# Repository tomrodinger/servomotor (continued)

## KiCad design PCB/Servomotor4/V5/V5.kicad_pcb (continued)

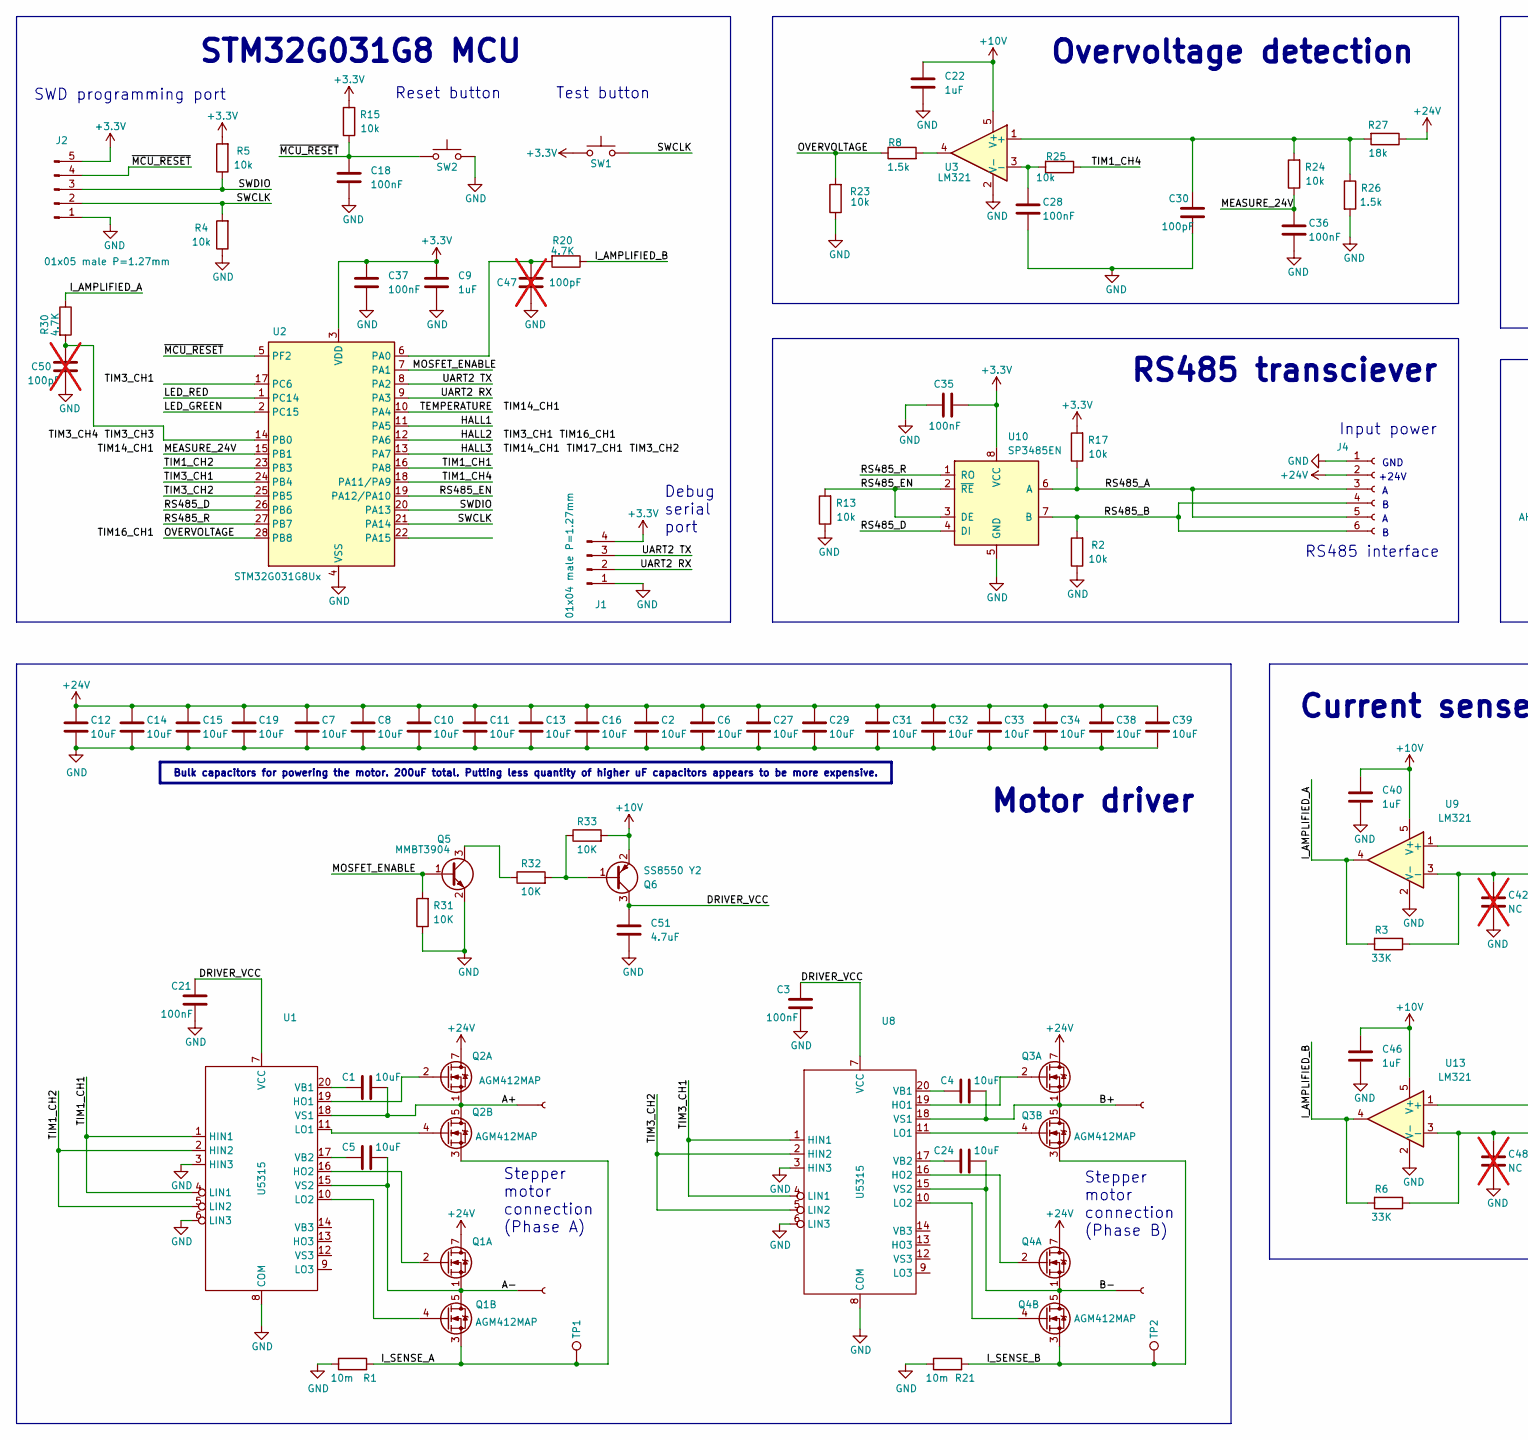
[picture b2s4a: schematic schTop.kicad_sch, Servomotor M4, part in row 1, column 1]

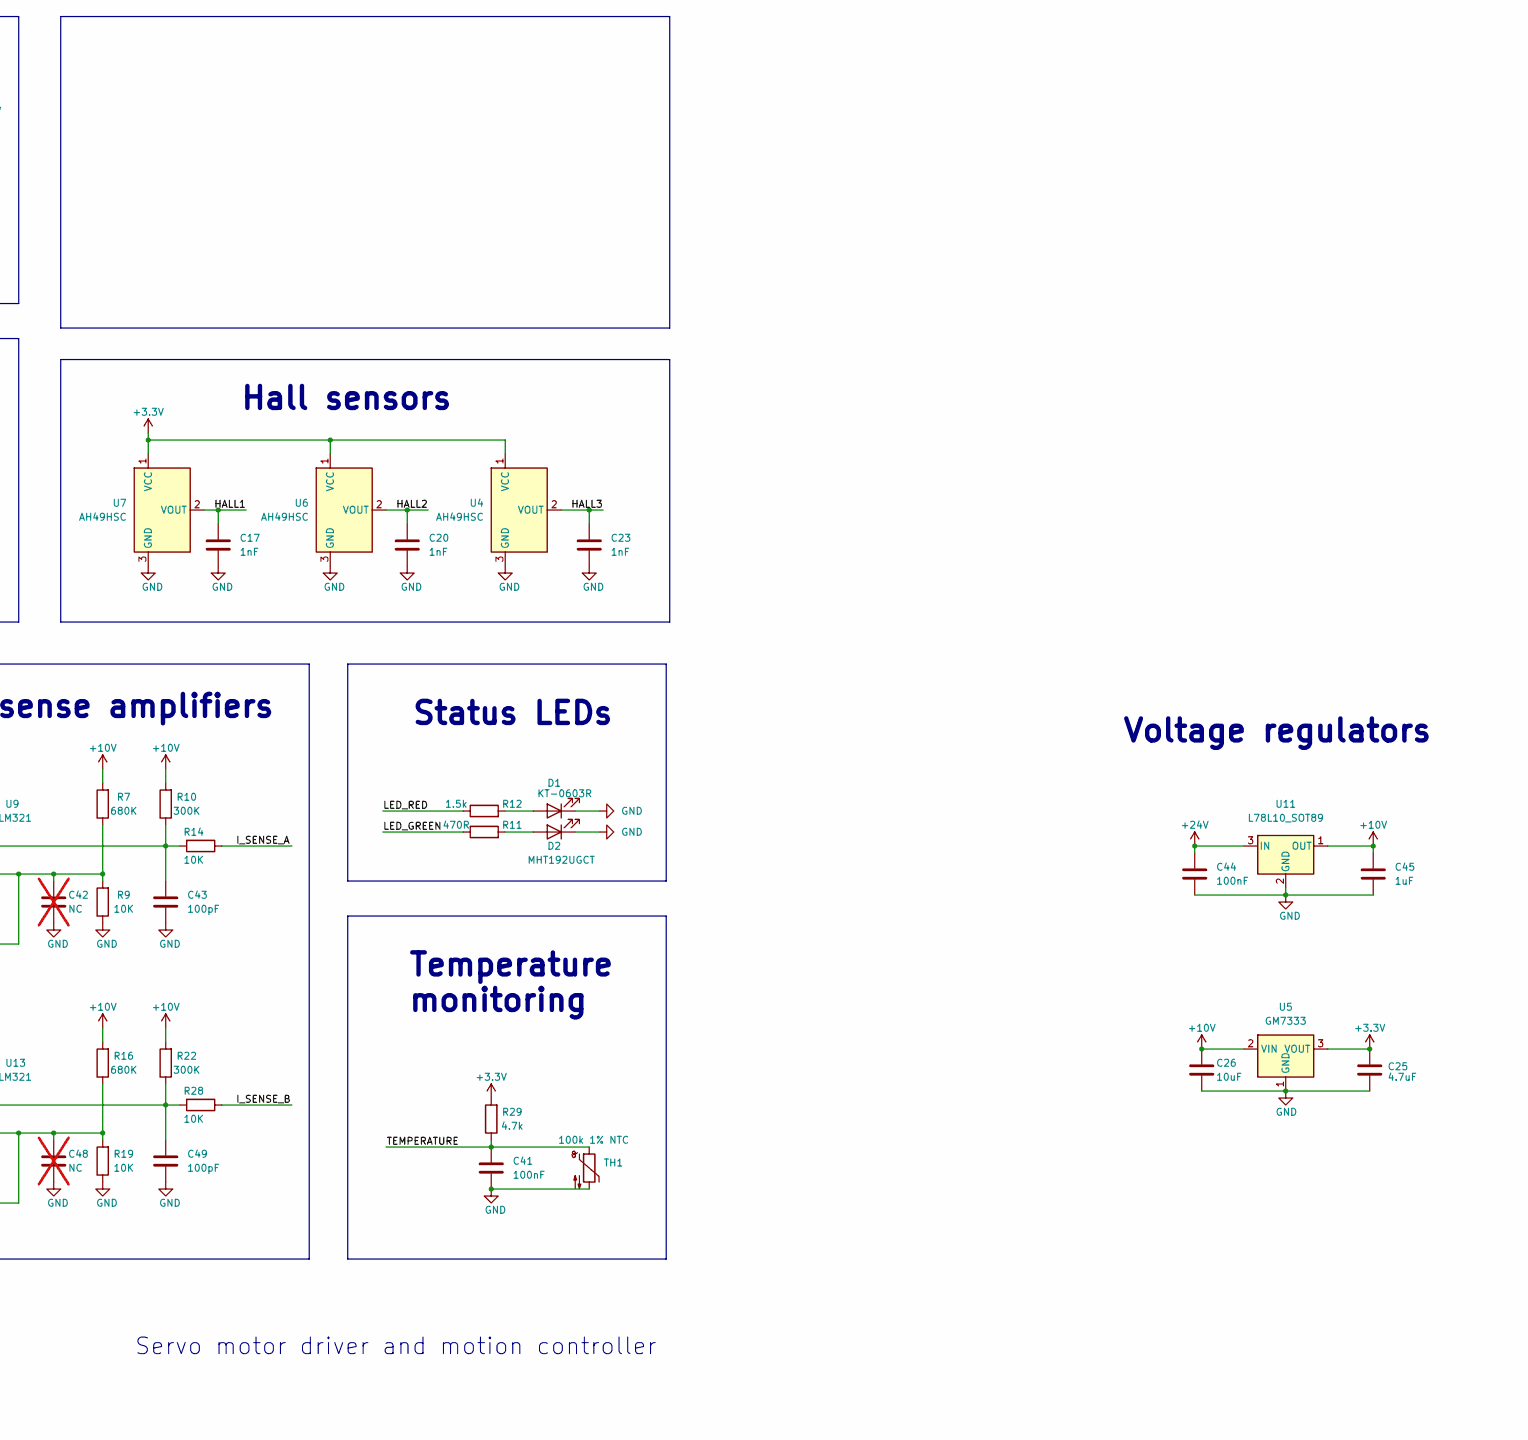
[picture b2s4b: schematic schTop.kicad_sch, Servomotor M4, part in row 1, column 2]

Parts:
C1, C4, C5, C24: 10uF; C_0603_1608Metric; LCSC C96446
C2, C6, C7, C8, C10, C11, C12, C13, C14, C15, C16, C19, C26, C27, C29, C31, C32, C33, C34, C38, C39: 10uF; C_0603_1608Metric; LCSC C194427
C3, C18, C21, C28, C35, C36, C37, C41: 100nF; C_0402_1005Metric; LCSC C307331
C9, C22: 1uF; C_0402_1005Metric; LCSC C52923
C17, C20, C23: 1nF; C_0402_1005Metric; LCSC C1523
C25: 4.7uF; C_0402_1005Metric; LCSC C23733
C30: 100pF; C_0402_1005Metric; LCSC C1546
C40, C45, C46: 1uF; C_0603_1608Metric; MPN CL10A105KB8NNNC; LCSC C15849
C42, C48: NC; C_0603_1608Metric; not fitted
C43, C49: 100pF; C_0603_1608Metric; MPN CL10C101JB8NNNC; LCSC C14858
C44: 100nF; C_0603_1608Metric; MPN CC0603KRX7R9BB104; LCSC C14663
C47, C50: 100pF; C_0402_1005Metric; LCSC C1546; not fitted
C51: 4.7uF; C_0603_1608Metric; MPN CL10A475KO8NNNC; LCSC C19666
D1: KT-0603R; LED_0603_1608Metric; LCSC C2286
D2: MHT192UGCT; LED_0603_1608Metric; LCSC C389519
J1: 01x04 male P=1.27mm; PinHeader_1x04_P1.27mm_Vertical
J2: 01x05 male P=1.27mm; PinHeader_1x05_P1.27mm_Vertical
J3, J5, J6, J8: Conn_01x01_Socket; Pad_3mm_TopOnly
J4: Conn_01x06_Socket; PinSocket_1x06_P2.00mm_Vertical
Q1, Q2, Q3, Q4: AGM412MAP; Diodes_PowerDI3333-8_UXC_3.3x3.3mm_P0.65mm; JLCPCB C5297500
Q5: MMBT3904; SOT-23; MPN MMBT3904; LCSC C20526
Q6: SS8550 Y2; SOT-23; MPN SS8550 Y2; LCSC C8542
R1, R21: 10m; R_2512_6332Metric; LCSC C105366
R2, R4, R5, R13, R15, R17, R23, R24, R25: 10k; R_0402_1005Metric; LCSC C25744
R3, R6: 33K; R_0603_1608Metric; MPN 0603WAF3302T5E; LCSC C4216
R7, R16: 680K; R_0603_1608Metric; MPN 0603WAF6803T5E; LCSC C25822
R8, R12, R26: 1.5k; R_0402_1005Metric; LCSC C25867
R9, R14, R19, R28: 10K; R_0603_1608Metric; MPN 0603WAF1002T5E; LCSC C25804
R10, R22: 300K; R_0603_1608Metric; MPN 0603WAF3003T5E; LCSC C23024
R11: 470R; R_0402_1005Metric; LCSC C25117
R20, R30: 4.7K; R_0402_1005Metric; LCSC C25900
R27: 18k; R_0603_1608Metric; LCSC C25810
R29: 4.7k; R_0402_1005Metric; LCSC C25900
R31, R32, R33: 10K; R_0402_1005Metric; LCSC C25744
SW1, SW2: TS3735PA-250gf; LCSC C393946
TH1: 100k 1% NTC; R_0402_1005Metric; LCSC C236279
TP1, TP2: TestPoint; TestPoint_Pad_D1.5mm
U1, U8: U5315; TSSOP-20_4.4x6.5mm_P0.65mm; LCSC C2892899
U2: STM32G031G8Ux; QFN-28_4x4mm_P0.5mm; LCSC C432211
U3: LM321; SOT-23-5; LCSC C19723728
U4, U6, U7: AH49HSC; SOT-23; LCSC C510723
U5: GM7333; SOT-89-3; LCSC C2833582
U9, U13: LM321; SOT-23-5; MPN LM321; LCSC C395460
U10: SP3485EN; SOIC-8_3.9x4.9mm_P1.27mm; LCSC C8963
U11: L78L10_SOT89; SOT-89-3; MPN 78L10; LCSC C122848

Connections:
+3.3V: C9.1, C25.1, C35.2, C37.1, J1.4, J2.5, R5.2, R15.2, R17.2, R29.2, SW1.1, U2.3 (VDD), U4.1 (VCC), U5.3 (VOUT), U6.1 (VCC), U7.1 (VCC), U10.8 (VCC)
+10V: C22.1, C26.1, C40.1, C45.1, C46.1, Q6.2 (E), R7.2, R10.2, R16.2, R22.2, R33.2, U3.5 (V+), U5.2 (VIN), U9.5 (V+), U11.1 (OUT), U13.5 (V+)
+24V: C2.1, C6.1, C7.1, C8.1, C10.1, C11.1, C12.1, C13.1, C14.1, C15.1, C16.1, C19.1, C27.1, C29.1, C31.1, C32.1, C33.1, C34.1, C38.1, C39.1, C44.1, J4.2, Q1.7 (D1), Q2.7 (D1), Q3.7 (D1), Q4.7 (D1), R27.1, U11.3 (IN)
/index/schTop/A+: C1.2, J8.1, Q2.1 (S1), Q2.5 (D2), U1.18 (VS1)
/index/schTop/A-: C5.2, J5.1, Q1.1 (S1), Q1.5 (D2), U1.15 (VS2)
/index/schTop/B+: C4.2, J3.1, Q3.1 (S1), Q3.5 (D2), U8.18 (VS1)
/index/schTop/B-: C24.2, J6.1, Q4.1 (S1), Q4.5 (D2), U8.15 (VS2)
/index/schTop/DRIVER_VCC: C3.1, C21.1, C51.1, Q6.3 (C), U1.7 (VCC), U8.7 (VCC)
/index/schTop/HALL1: C17.1, U2.11 (PA5), U7.2 (VOUT)
/index/schTop/HALL2: C20.1, U2.12 (PA6), U6.2 (VOUT)
/index/schTop/HALL3: C23.1, U2.13 (PA7), U4.2 (VOUT)
/index/schTop/I_AMPLIFIED_A: R3.2, R30.1, U9.4
/index/schTop/I_AMPLIFIED_B: R6.2, R20.1, U13.4
/index/schTop/I_SENSE_A: Q1.3 (S2), Q2.3 (S2), R1.2, R14.1, TP1.1
/index/schTop/I_SENSE_B: Q3.3 (S2), Q4.3 (S2), R21.2, R28.1, TP2.1
/index/schTop/LED_GREEN: R11.1, U2.2 (PC15)
/index/schTop/LED_RED: R12.1, U2.1 (PC14)
/index/schTop/MEASURE_24V: C36.1, R24.1, U2.15 (PB1)
/index/schTop/MOSFET_ENABLE: Q5.1 (B), R31.2, U2.7 (PA1)
/index/schTop/OVERVOLTAGE: R8.1, R23.2, U2.28 (PB8)
/index/schTop/RS485_A: J4.3, J4.5, R17.1, U10.6 (A)
/index/schTop/RS485_B: J4.4, J4.6, R2.2, U10.7 (B)
/index/schTop/RS485_D: U2.26 (PB6), U10.4 (DI)
/index/schTop/RS485_EN: R13.2, U2.19 (PA12/PA10), U10.2 (~RE), U10.3 (DE)
/index/schTop/RS485_R: U2.27 (PB7), U10.1 (RO)
/index/schTop/SWCLK: J2.2, R4.2, SW1.2, U2.21 (PA14)
/index/schTop/SWDIO: J2.3, R5.1, U2.20 (PA13)
/index/schTop/TEMPERATURE: C41.1, R29.1, TH1.1, U2.10 (PA4)
/index/schTop/TIM1_CH1: U1.1 (HIN1), U1.4 (LIN1), U2.16 (PA8)
/index/schTop/TIM1_CH2: U1.2 (HIN2), U1.5 (LIN2), U2.23 (PB3)
/index/schTop/TIM1_CH4: R25.1, U2.18 (PA11/PA9)
/index/schTop/TIM3_CH1: U2.24 (PB4), U8.1 (HIN1), U8.4 (LIN1)
/index/schTop/TIM3_CH2: U2.25 (PB5), U8.2 (HIN2), U8.5 (LIN2)
/index/schTop/UART2 RX: J1.2, U2.9 (PA3)
/index/schTop/UART2 TX: J1.3, U2.8 (PA2)
/index/schTop/~MCU_RESET: C18.1, J2.4, R15.1, SW2.1, U2.5 (PF2)
GND: C2.2, C3.2, C6.2, C7.2, C8.2, C9.2, C10.2, C11.2, C12.2, C13.2, C14.2, C15.2, C16.2, C17.2, C18.2, C19.2, C20.2, C21.2, C22.2, C23.2, C25.2, C26.2, C27.2, C28.2, C29.2, C30.2, C31.2, C32.2, C33.2, C34.2, C35.1, C36.2, C37.2, C38.2, C39.2, C40.2, C41.2, C42.2, C43.2, C44.2, C45.2, C46.2, C47.2, C48.2, C49.2, C50.2, C51.2, D1.1 (K), D2.1 (K), J1.1, J2.1, J4.1, Q5.2 (E), R1.1, R2.1, R4.1, R9.1, R13.1, R19.1, R21.1, R23.1, R26.2, R31.1, SW2.2, TH1.2, U1.3 (HIN3), U1.6 (LIN3), U1.8 (COM), U2.4 (VSS), U3.2 (V-), U4.3 (GND), U5.1 (GND), U6.3 (GND), U7.3 (GND), U8.3 (HIN3), U8.6 (LIN3), U8.8 (COM), U9.2 (V-), U10.5 (GND), U11.2 (GND), U13.2 (V-)
unnamed: Q1.2 (G1), U1.16 (HO2)
unnamed: Q1.4 (G2), U1.10 (LO2)
unnamed: Q2.2 (G1), U1.19 (HO1)
unnamed: Q2.4 (G2), U1.11 (LO1)
unnamed: Q3.2 (G1), U8.19 (HO1)
unnamed: Q3.4 (G2), U8.11 (LO1)
unnamed: Q4.2 (G1), U8.16 (HO2)
unnamed: Q4.4 (G2), U8.10 (LO2)
unnamed: Q5.3 (C), R32.1
unnamed: Q6.1 (B), R32.2, R33.1
unnamed: R8.2, U3.4
unnamed: C5.1, U1.17 (VB2)
unnamed: C1.1, U1.20 (VB1)
unnamed: C47.1, R20.2, U2.6 (PA0)
unnamed: C50.1, R30.2, U2.14 (PB0)
unnamed: C30.1, R24.2, R26.1, R27.2, U3.1 (+)
unnamed: C28.1, R25.2, U3.3 (-)
unnamed: C24.1, U8.17 (VB2)
unnamed: C4.1, U8.20 (VB1)
unnamed: C43.1, R10.1, R14.2, U9.1 (+)
unnamed: C42.1, R3.1, R7.1, R9.2, U9.3 (-)
unnamed: C49.1, R22.1, R28.2, U13.1 (+)
unnamed: C48.1, R6.1, R16.1, R19.2, U13.3 (-)

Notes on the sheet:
Bulk capacitors for powering the motor. 200uF total. Putting less quantity of higher uF capacitors appears to be more expensive.
Reset button
Test button
+24V
SWD programming port
Debug serial port
GND
RS485 transciever
Input power
Status LEDs
Overvoltage detection
Stepper motor connection (Phase B)
Voltage regulators
Current sense amplifiers
RS485 interface
Temperature monitoring
Servo motor driver and motion controller
STM32G031G8 MCU
Motor driver
Hall sensors
Stepper motor connection (Phase A)

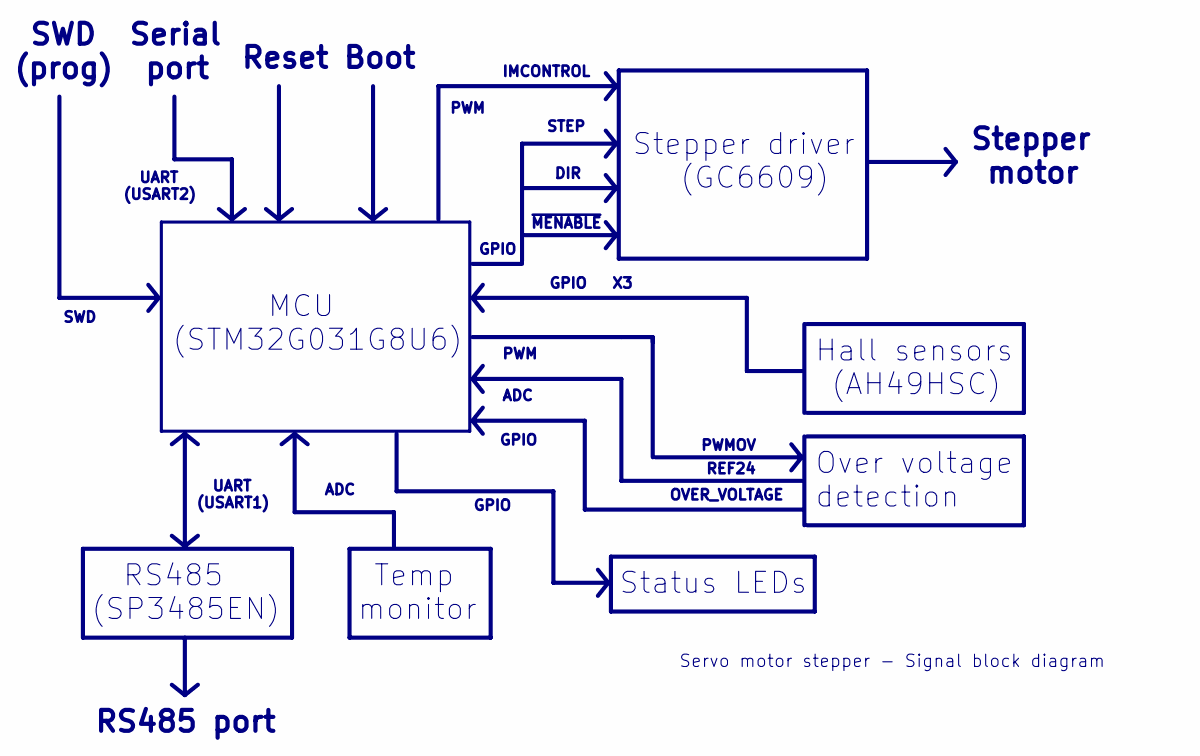
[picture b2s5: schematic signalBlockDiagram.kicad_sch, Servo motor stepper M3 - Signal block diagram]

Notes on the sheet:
~{MENABLE}
Stepper driver (GC6609)
Serial port
REF24
RS485 (SP3485EN)
Temp monitor
UART (USART2)
MCU (STM32G031G8U6)
IMCONTROL
ADC
UART (USART1)
PWM
GPIO
STEP
SWD (prog)
Over voltage detection
OVER_VOLTAGE
Status LEDs
Boot
PWMOV
Reset
DIR
Stepper motor
RS485 port
Servo motor stepper - Signal block diagram
Hall sensors (AH49HSC)
SWD

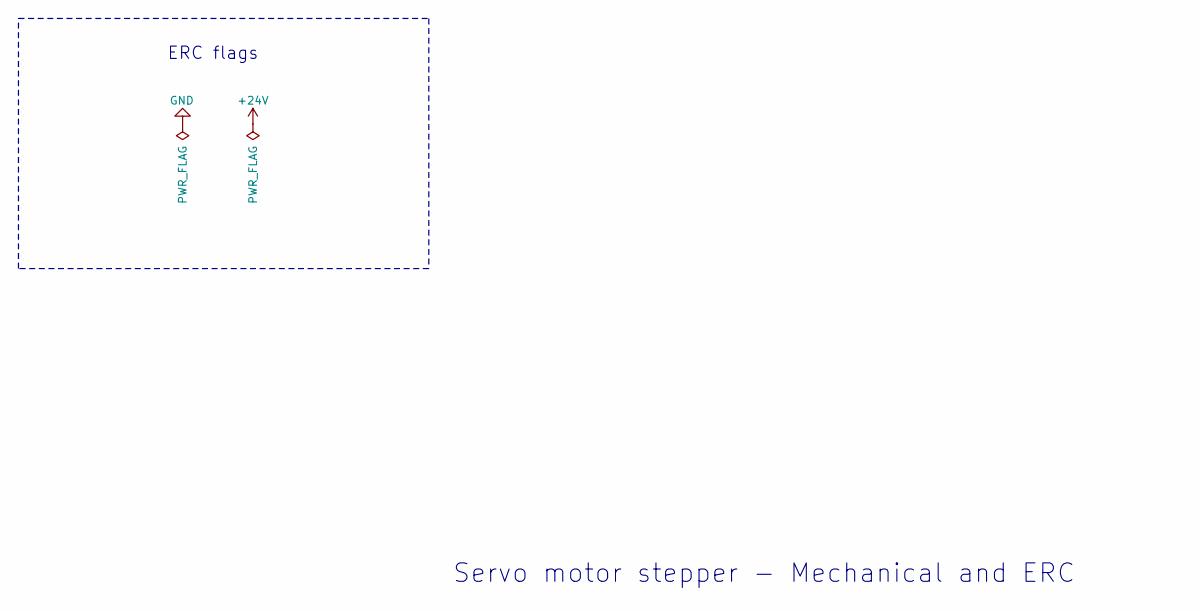
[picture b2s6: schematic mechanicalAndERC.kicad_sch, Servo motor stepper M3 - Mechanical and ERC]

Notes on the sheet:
ERC flags
Servo motor stepper - Mechanical and ERC

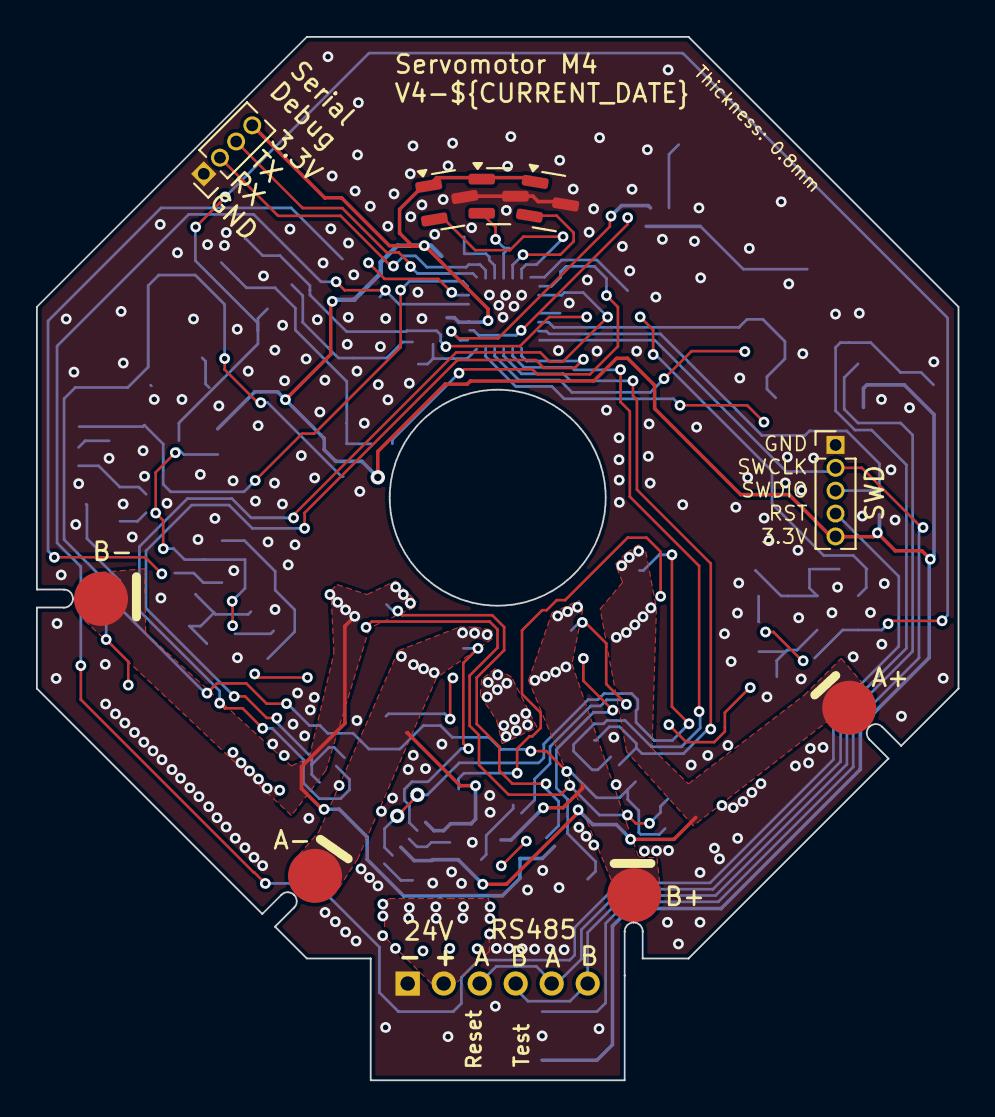
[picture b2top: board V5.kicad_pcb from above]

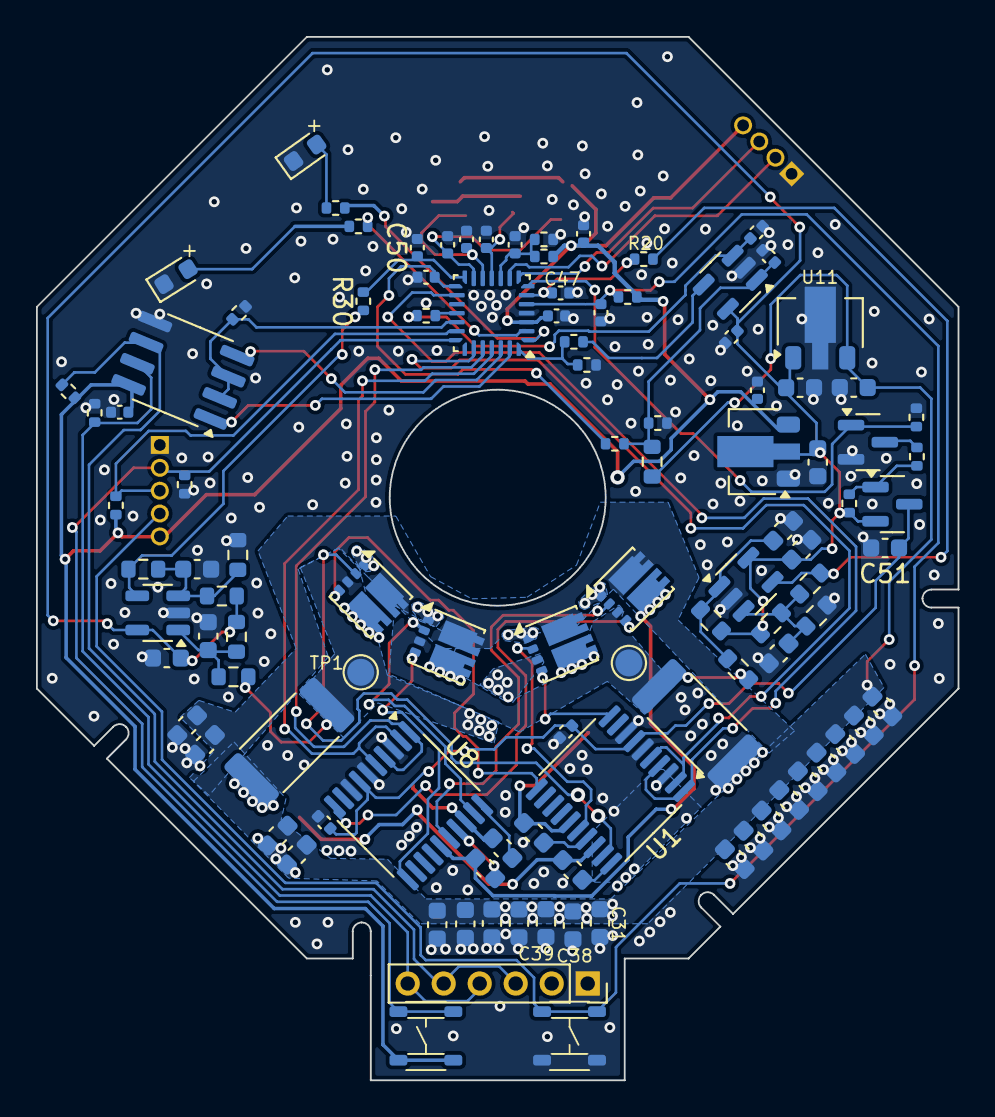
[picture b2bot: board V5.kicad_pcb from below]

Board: 2 copper layers, 51.2 x 58.0 mm, 115 parts (106 on the bottom side), 60 nets.

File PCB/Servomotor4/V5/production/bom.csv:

Designator,Footprint,Quantity,Value,LCSC Part #
"C1, C24, C4, C5",0603,4,10uF,C96446
"C10, C11, C12, C13, C14, C15, C16, C19, C2, C26, C27, C29, C31, C32, C33, C34, C38, C39, C6, C7, C8",0603,21,10uF,C194427
"C17, C20, C23",0402,3,1nF,C1523
"C18, C21, C28, C3, C35, C36, C37, C41",0402,8,100nF,C307331
"C22, C9",0402,2,1uF,C52923
C25,0402,1,4.7uF,C23733
C30,0402,1,100pF,C1546
"C40, C45, C46",0603,3,1uF,C15849
"C43, C49",0603,2,100pF,C14858
C44,0603,1,100nF,C14663
C51,0603,1,4.7uF,C19666
D1,0603,1,KT-0603R,C2286
D2,0603,1,MHT192UGCT,C389519
J4,PinSocket_1x06_P2.00mm_Vertical,1,Conn_01x06_Socket,
"Q1, Q2, Q3, Q4",Diodes_PowerDI3333-8_UXC_3.3x3.3mm_P0.65mm,4,AGM412MAP,C5297500
Q5,SOT-23,1,MMBT3904,C20526
Q6,SOT-23,1,SS8550 Y2,C8542
"R1, R21",2512,2,10m,C105366
"R10, R22",0603,2,300K,C23024
R11,0402,1,470R,C25117
"R12, R26, R8",0402,3,1.5k,C25867
"R13, R15, R17, R2, R23, R24, R25, R31, R32, R33, R4, R5",0402,12,10k,C25744
"R14, R19, R28, R9",0603,4,10K,C25804
"R16, R7",0603,2,680K,C25822
"R20, R29, R30",0402,3,4.7K,C25900
R27,0603,1,18k,C25810
"R3, R6",0603,2,33K,C4216
"SW1, SW2",TS3735PA-250gf,2,TS3735PA-250gf,C393946
TH1,0402,1,100k 1% NTC,C236279
"TP1, TP2",TestPoint_Pad_D1.5mm,2,TestPoint,
"U1, U8",TSSOP-20_4.4x6.5mm_P0.65mm,2,U5315,C2892899
U10,SOIC-8_3.9x4.9mm_P1.27mm,1,SP3485EN,C8963
U11,SOT-89-3,1,L78L10_SOT89,C122848
"U13, U9",SOT-23-5,2,LM321,C395460
U2,QFN-28_4x4mm_P0.5mm,1,STM32G031G8Ux,C432211
U3,SOT-23-5,1,LM321,C19723728
"U4, U6, U7",SOT-23,3,AH49HSC,C510723
U5,SOT-89-3,1,GM7333,C2833582

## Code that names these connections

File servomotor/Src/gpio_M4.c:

#include "stm32g0xx_hal.h"
#include "gpio.h"

#define BUTTON_PORT_A_PIN 14 // products M3 and M4
#define TOUCH_BUTTON_PORT_A_PIN 15

static void portA_init(void)
{
    GPIOA->MODER =
            (MODER_ANALOG_INPUT       << GPIO_MODER_MODE0_Pos)  | // Amplified motor current sense voltage (Phase A)
            (MODER_DIGITAL_OUTPUT     << GPIO_MODER_MODE1_Pos)  | // MOSFET enable control (active high)
            (MODER_ALTERNATE_FUNCTION << GPIO_MODER_MODE2_Pos)  | // serial port TX
            (MODER_ALTERNATE_FUNCTION << GPIO_MODER_MODE3_Pos)  | // serial port RX
            (MODER_ANALOG_INPUT       << GPIO_MODER_MODE4_Pos)  | // Temperature sensor (NTC) analog input
            (MODER_ANALOG_INPUT       << GPIO_MODER_MODE5_Pos)  | // Hall sensor 1 analog input
            (MODER_ANALOG_INPUT       << GPIO_MODER_MODE6_Pos)  | // Hall sensor 2 analog input
            (MODER_ANALOG_INPUT       << GPIO_MODER_MODE7_Pos)  | // Hall sensor 3 analog input
            (MODER_ALTERNATE_FUNCTION << GPIO_MODER_MODE8_Pos)  | // Motor phase A voltage control PWM output (TIM1_CH1)
            (MODER_ANALOG_INPUT       << GPIO_MODER_MODE9_Pos)  | // Don't use. Might be connected tp PA11 internally
            (MODER_ANALOG_INPUT       << GPIO_MODER_MODE10_Pos) | // Don't use. Might be connected tp PA12 internally
            (MODER_ALTERNATE_FUNCTION << GPIO_MODER_MODE11_Pos) | // Overvoltage setting PWM output (to set the overvoltage threshold) by TIM1_CH4
            (MODER_ALTERNATE_FUNCTION << GPIO_MODER_MODE12_Pos) | // RS485 Data enable (DE) output
            (MODER_ANALOG_INPUT       << GPIO_MODER_MODE13_Pos) | // SWDIO (for programming)
            (MODER_DIGITAL_INPUT      << GPIO_MODER_MODE14_Pos) | // SWCLK (for programming) and button input
            (MODER_DIGITAL_OUTPUT     << GPIO_MODER_MODE15_Pos);  //

//    GPIOA->OTYPER = (OTYPER_OPEN_DRAIN << GPIO_OTYPER_OT1_Pos) | // make all the pins with analog components connected open drain
//                    (OTYPER_OPEN_DRAIN << GPIO_OTYPER_OT3_Pos) | // also, make the RS485 receive pin open drain
//                    (OTYPER_OPEN_DRAIN << GPIO_OTYPER_OT4_Pos) | // may not be necessary
//                    (OTYPER_OPEN_DRAIN << GPIO_OTYPER_OT5_Pos) |
//                    (OTYPER_OPEN_DRAIN << GPIO_OTYPER_OT6_Pos) |
//                    (OTYPER_OPEN_DRAIN << GPIO_OTYPER_OT8_Pos) |
//                    (OTYPER_OPEN_DRAIN << GPIO_OTYPER_OT9_Pos) |
//                    (OTYPER_OPEN_DRAIN << GPIO_OTYPER_OT10_Pos) |
//                    (OTYPER_OPEN_DRAIN << GPIO_OTYPER_OT13_Pos) |
//                    (OTYPER_OPEN_DRAIN << GPIO_OTYPER_OT14_Pos);
    GPIOA->OSPEEDR = 0xffffffff; // make all pins very high speed
    GPIOA->PUPDR = (PUPDR_PULL_UP << GPIO_PUPDR_PUPD3_Pos); // apply pull up on the RS485 receive pin
    GPIOA->BSRR = ((1 << 1) << 16); // set the MOSFET enable line low so that the motor driver is disabled to start with
}


static void portB_init(void)
{
    GPIOB->MODER =
            (MODER_ANALOG_INPUT       << GPIO_MODER_MODE0_Pos)  | // Amplified motor current sense voltage (Phase B)
            (MODER_ANALOG_INPUT       << GPIO_MODER_MODE1_Pos)  | // Supply voltage (24V) analog input (after divider)
            (MODER_ALTERNATE_FUNCTION << GPIO_MODER_MODE3_Pos)  | // Motor phase A voltage control PWM output (TIM1_CH2)
            (MODER_ALTERNATE_FUNCTION << GPIO_MODER_MODE4_Pos)  | // Motor phase B voltage control PWM output (TIM3_CH1)
            (MODER_ALTERNATE_FUNCTION << GPIO_MODER_MODE5_Pos)  | // Motor phase B voltage control PWM output (TIM3_CH2)
            (MODER_ALTERNATE_FUNCTION << GPIO_MODER_MODE6_Pos)  | // RS485 Data out
            (MODER_ALTERNATE_FUNCTION << GPIO_MODER_MODE7_Pos)  | // RS485 Data receive
            (MODER_DIGITAL_INPUT      << GPIO_MODER_MODE8_Pos)  | // Overvoltage digital input (will shut off motor driver very fast if trigered)
            (MODER_ANALOG_INPUT       << GPIO_MODER_MODE9_Pos)  |
            (MODER_ANALOG_INPUT       << GPIO_MODER_MODE10_Pos) |
            (MODER_ANALOG_INPUT       << GPIO_MODER_MODE11_Pos) |
            (MODER_ANALOG_INPUT       << GPIO_MODER_MODE12_Pos) |
            (MODER_ANALOG_INPUT       << GPIO_MODER_MODE13_Pos) |
            (MODER_ANALOG_INPUT       << GPIO_MODER_MODE14_Pos) |
            (MODER_ANALOG_INPUT       << GPIO_MODER_MODE15_Pos);

//    GPIOB->OTYPER = (OTYPER_OPEN_DRAIN << GPIO_OTYPER_OT1_Pos) | // Make the analog input pins open drain
//                  (OTYPER_OPEN_DRAIN << GPIO_OTYPER_OT4_Pos) |
//                  (OTYPER_OPEN_DRAIN << GPIO_OTYPER_OT5_Pos) |
//                  (OTYPER_OPEN_DRAIN << GPIO_OTYPER_OT7_Pos) | // RX pin make as open drain
//                  (OTYPER_OPEN_DRAIN << GPIO_OTYPER_OT8_Pos);  // Overvoltage digital input make as open drain
    GPIOB->OSPEEDR = 0xffffffff; // make all pins very high speed
    GPIOB->PUPDR = (PUPDR_PULL_UP   << GPIO_PUPDR_PUPD7_Pos) | // RX pin is pull up
                   (PUPDR_PULL_DOWN << GPIO_PUPDR_PUPD8_Pos);  // overvoltage pin is pull down
}


static void portC_init(void)
{
    GPIOC->MODER =
            (MODER_DIGITAL_OUTPUT     << GPIO_MODER_MODE6_Pos)  | //
            (MODER_DIGITAL_OUTPUT     << GPIO_MODER_MODE14_Pos) | // Red LED
            (MODER_DIGITAL_OUTPUT     << GPIO_MODER_MODE15_Pos);  // Green LED
//    GPIOC->OTYPER = (0);  // Make the analog input pins open drain
    GPIOC->OSPEEDR = 0xffffffff; // very high speed
    GPIOC->PUPDR = 0; // no pins have pulling resistors
}


void GPIO_init_M4(void)
{
    portA_init();
    portB_init();
    portC_init();
}

inline uint8_t get_button_state_M4(void)
{
    return ((GPIOA->IDR & (1 << BUTTON_PORT_A_PIN)) != 0);
}

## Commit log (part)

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2023-12-11 Adding a new test program for testing the time sync function to one device.
2023-12-12 Some cleanups. Some improved printing of data. A new test program for testing the time sync across multiple devices.
2023-12-19 Some cleanups
2024-01-09 Adding the convertion to degrees C in the extruder project Extruder heater will now always shut off when there is a fatal error
2024-01-09 Some data from testing 11 magnetic rings
2024-01-12 Adding a program to make some graphs showing the weights and also calculating the average values of the weights.
2024-01-19 Now it won't write out the png file until all trials are done, to speed up the processing.
2024-02-24 Updating product data information for Servomotor#3
2024-05-15 Adding support for Servomotor#4 Adding test mode for LEDs where they all turn on Bug fixes
2024-05-22 Adding another command that lets you change the PID constants.
2024-06-17 Updating data for Servomotor#3 V7
2024-07-23 Improved PID parameter handling. Ability to read PID control loop variables back through the RS485 interace for debugging purposes.
2024-09-14 Forgot to commit some files in the last commit, so commiting them now Refactoring the GPIO initialization codes for the different servomotors into different files
2024-09-27 Adding a Python program that cleans the git repository by moving untracked files to a separate folder. It was written by ChatGPT, so use at own risk.
2024-10-12 Adjusting parameters of GC6609 chip in Servomotor#3 to decrease high pitch noise Supply voltage calibration Removing unneeded code Overvoltage protection calibration Rename of PWM_PERIOD into two dif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
2024-10-16 Adjusting parameters to make the current control more stable and not too high of a switching frequency.
2024-10-16 Adding new PCB designs for Servomotor#3 and Servomotor#4
2024-10-17 Updating the algorithm for the hall sensors so that we can support cases where one rotation does not need to have a number of microsteps that is divisible by 3. This will allow us to suuport a case w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
2024-10-18 Setting up to measure the current through phase B Adding analog watchdog 3 in to monitor the current of phase B Disabling the ADC interrupt for now, because it seems to be triggering undesirably, pro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
2024-11-13 Fix a mistake with a wrong import
2024-11-16 iStrangely, this firmware does not work. Motor cannot enable and spin. DON'T USE THIS FIRMWARE. Adding a test program for testing the PID controller Adding a "Set Max allowable position deviation" co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
2024-11-20 more coloutful logging to the screen Added a test program for testing the terminal formatting.
2024-11-23 All calls to fatal_error() no longer have a hard coded magic number and instead us an enum in there. Debug printing from the servomotor will be disabled by default, and will only become enabled if a 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
2024-11-24 Bootloader will now use product specific GPIO initialization code. That code is moved to the common_source_files directory.
2024-11-25 Fixing issues with the GPIO initialization in the bootloader and the application firmware. Fixing the build_and_program.sh script that builds the bootloader, because it was not adding device specific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
2024-12-02 updating the pictures
2024-12-05 Adding some .gitignores to clean up git status Files that store bootloader bin files and also servomotor firmware files are renamed a bit to have more descriptive information
2024-12-10 the calculated transformation matrix tweaks to the calibrate_glue_machine.py program
2025-01-03 Changing the GET_DEBUG_VALUES_COMMAND command to have value of 45 instead of 253.
2025-01-03 fixing a link to the schematic for M3 V11
2025-01-10 Beginnings of a Arduino library and a C SDK. A partially working motor simulator that visualizes the motor spinning and which uses a lot of the actual servomotor firmware. load_global_settings and sa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
2025-02-17 The calculation of the hal sensors' ADC values is working correctly now and the encoder will correctly calculate the motor shaft's position. Removal of redundant variables that store the shaft angle.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
2025-02-20 Solving compile errors. It compiles and runs now, but does not yet send and receive information through a serial port.
2025-02-22 Fixed one of the TODOs. Now in the main Arduino program we do not need to do dynamic memory allocation. If the serial port can't be opened then an error will be printed and the program will exit. Upd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
2025-02-23 Adding a build script for building some test programs. Fix one compile warning with one of the tests.
2025-02-26 Adding init routines to initialize some of the static variables when a System reset command is issued. Adding various debug print statements. Reset procedure is now multistep to ensure that a fatal e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
2025-03-01 Fixing certain conversion constants for the velocity and acceleration that were wrongly calculated. Changed the unit conversion function to have a direction input to determine if it converts to or fr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
2025-03-02 Finished another TODO, which is to update the sript that copies the Arduino library relevant files. Adding more files to the .gitignores Renamed files that were exmaples rather than tests
2025-03-02 Renaming some cases of ServoMotor to Servomotor Renaming the examples Fixing a bunch of compiler warnings in the motor simulator compilation
2025-03-05 Arduino project now compiles and runs on real hardware. Renaming the ServoMotor class to Servomotor copy_stuff_to_Arduino.sh adjusted to make the right directory structures for compiling in the Ardui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
2025-03-06 More clear information at the top of autogenerated files to indicate that they are autogenerated, what generated them and when were they generated. The COUNTS_PER_REVOLUTION #define is now taken from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
2025-03-07 Fix multiMove functionality and add comprehensive testing Modifications were done to Servomotor.cpp and Servomotor.h directly, and we have not gotten to the changes required to autogenerate these yet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
2025-03-10 Preparing some things to get ready to submit to the Arduino ecosystem.
2025-03-18 Refactoring: taking the crc32 calculation routines out of settings.c and placing them in their own file
2025-03-24 Some refactoring so that the memory used for the receive buffer can be different in the motor firmware vs. the bootloader, because these have different requirements for the maximum mesage size sent t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
2025-03-25 Fixing the bootloader for the STM32G030 so that it uses the new protocol and compiles, although it is untested Adding some documentation about how to bring old main.c files up to date to use the new 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
2025-03-29 "Set device alias" and "Identify" commands no longer take a unique ID as an explicit parameter. Not needed anymore because the protocol now has a built in extended addressing mode "Get update frequen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
2025-03-31 A new reworked capture_hall_sensor_data.py program to get the hall sensor reading while spinning the motor, so that the sensors and magnetic disk can be verified to work correctly. communication.py i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
2025-04-03 When calling the Set device alias command, now we will check for a valid alias and prevent invalid aliases from being assigned Fixed a bug where the Detect devices commands sent incomplete data becau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
2025-04-07 The test framework now supports specifying a unique ID when running a test. It is specified on the command line. Rewrote the code that sends out a packet when using a unique ID addressing. Previous v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
2025-04-12 Make certain debug prints optional by having #define VERBOSE uncommented at the start of the source code file A check to make sure that if a very long packet is being sent then the size does not exce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
2025-04-13 Servomotor.cpp is now autogenerated. All tests compile and pass. This concludes the work to revamp the autogeneration code to the newer more clean and maintainable version Some refinements to the var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
2025-04-14 Fixed an issue where the Servomotor.h file when autogenerated did not have the correct overloaded functions
2025-04-23 Adding a new test to test the "Set device alias" command Adding a program that can run many tests in one shot called run_all_tests.py Adding a piece of documentation that has a list of the various te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
2025-06-12 Updating some product data
2025-06-18 Fixing a bunch of tests so that they can be automatically run one by one from the master program called run_all_tests.py and so that they all pass.
2025-06-20 New firmware released, nearly the same like the previous version, mainly used for testing the firmware upgrade program Fair bit of clean up around for the alias and unique ID are handles, not cleanly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
2025-06-28 Improvements on the detection of connected devices. Solve the issue where the device got into the bootloader unexpectedly. Bumping firmware version a little Code cleanups Releasing a firmware for har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
2025-07-02 Fixing two tests because they got broken when I made the recent changes to the device behaviour during fatal error and I changed the protocol slightly.
2025-07-12 Adding the new product M17, which is a rename of M3
2025-07-25 Updating the documentation regarding the communication protocol because a few things were not correct anymore.
2025-08-26 adding a folder
2025-08-26 adding pictures
2025-08-26 adding M17-60 pictures
2025-08-30 Making a new version of the datasheet where some corrections are made and also some improvements.
2025-08-31 A new version of the datasheet that adds example programs, and information about the Python and Arduino libraries.
2025-09-01 Add servomotor marketing page autogeneration system
    - Converts existing PDF datasheet generator into HTML marketing page generator
    - Creates responsive HTML + CSS output for e-commerce site integration
    - Includes web_utils.py and web_styles.py for HTML/CSS generation
    - Generates marketing.html and marketing.css from content files
    - Adds company profile and applications sections with product images
    - Maintains all original content while optimizing for web presentation
2025-09-12 Updating the examples of the Python and Arduino codes with ones that actually are right and work. Regenerating the API documents.
2025-09-12 the motor_command.py program has changed to servomotor_command.py, so I am changing all references to it in the documentation, etc.
2025-09-12 Fixing the autogenerator of the Aurduino library code so that it generates the latest version of the Arduino library that correctly runs examples and what not
2025-09-15 Updating the generator of the marketting page to generate a preview and the content for the ecommerce site in one shot and the content should be the same in each.
2025-10-12 making a static link to the connection diagram from the datasheet version so that they is only one source of truth fixing the link to the tutorial on the marketting page (ot tutorial.gearotons.com) a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
2025-10-17 Fix YAML version formatting for product M17
2025-11-21 Fixing a broken link to the tutorial for servomotor version 1.3
2025-12-28 Changing the types of some variables to solve issues. Commands affected: Get product info Timy Sync Get hardware version
2025-12-28 Fix the program that captures the hall sensor data to work more reliably in the case of an uncalibrated motor or one with faulty magnets or hall sensory. basically, we allow a huge position deviation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
2025-12-28 Commenting out unused code
2025-12-30 Makefile now allows building for the programming test jig Changing the way hall sensor readings are processed. No more << 3 - HALL_SENSOR_SHIFT and instead we just take the hall sensor readings as is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
2026-02-03 Adding version 1.5 of the PCB for Servomotor M17
2026-02-03 Touchups on the marketting page
